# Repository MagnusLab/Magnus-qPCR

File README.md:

# 
An open, portable and low cost qPCR machine.

## WE ARE ACCEPTING [DONATIONS](https://www.vakinha.com.br/vaquinha/nos-ajude-a-desenvolver-uma-maquina-de-qpcr-a-baixo-custo)!: 

## Specifications*:
* 8 samples
* 1 to 4 channels, you can customize it!
  * FAM/Sybr Green
  * HEX
  * ROX/Cal Red 610
  * Cy5
* MicroSD card slot for data logging
* High Resolution Melting Analysis
* WiFi interface, so you can control and visualize data from a smartphone/PC
* Portable (less than 150 mm in size)
* USB powered (5V 3A power supply)
* CHEAP

**This machine is a work in progress, so the specifications may change and/or be innacurate. Also, don't try to replicate it if you don't know what you're doing, as it probably won't work until we release a stable version.*

## How will it work?
The machine can be roughly separated into 3 parts:

* The main PCB, containing the microcontroller and the heater;
* The PCB of the reading head, containing LEDs and light sensors;
* The optical reading head, which will house lenses, beam splitters, filters, prisms, etc., as well as the stepper motor responsible for positioning this optical assembly above each tube;

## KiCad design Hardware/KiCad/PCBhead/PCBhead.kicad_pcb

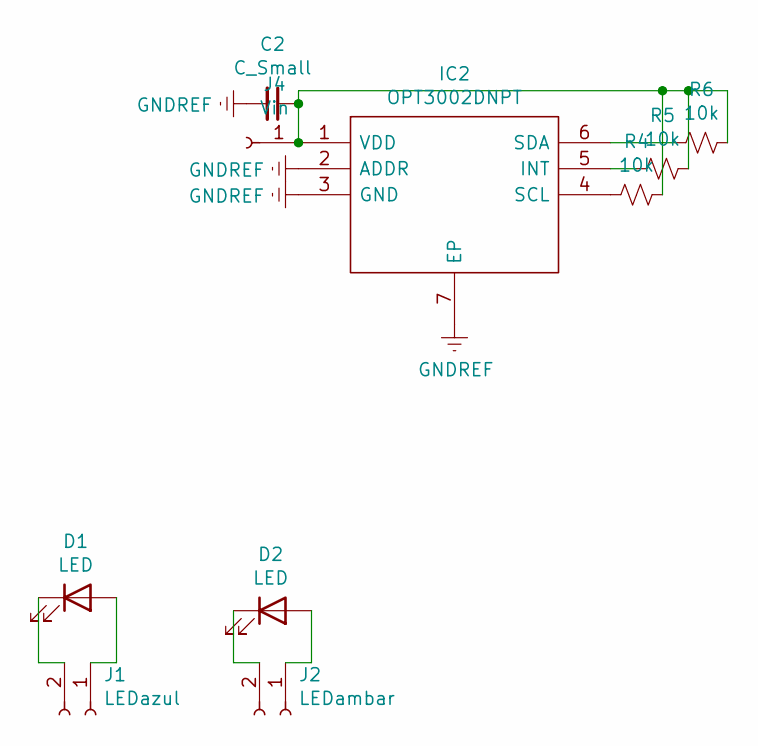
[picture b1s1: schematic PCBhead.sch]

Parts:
C2: C_Small; C_0805_2012Metric
D1, D2: LED
IC2: OPT3002DNPT; SON65P200X200X65-7N-D; Mouser Part Number 595-OPT3002DNPT
J1: LEDazul; PinSocket_1x02_P2.54mm_Horizontal
J2: LEDambar; PinSocket_1x02_P2.54mm_Horizontal
J4: Vin; PinSocket_1x01_P2.54mm_Horizontal
R4, R5, R6: 10k; R_0805_2012Metric

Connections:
GNDREF: C2.2, IC2.2 (ADDR), IC2.3 (GND), IC2.7 (EP)
unnamed: C2.1, IC2.1 (VDD), J4.1, R4.1, R5.1, R6.1
unnamed: D1.1 (K), J1.2
unnamed: D1.2 (A), J1.1
unnamed: D2.1 (K), J2.2
unnamed: D2.2 (A), J2.1
unnamed: IC2.4 (SCL), R4.2
unnamed: IC2.5 (INT), R5.2
unnamed: IC2.6 (SDA), R6.2

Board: 2 copper layers, 10 parts (7 on the bottom side), 9 nets, no tracks yet.

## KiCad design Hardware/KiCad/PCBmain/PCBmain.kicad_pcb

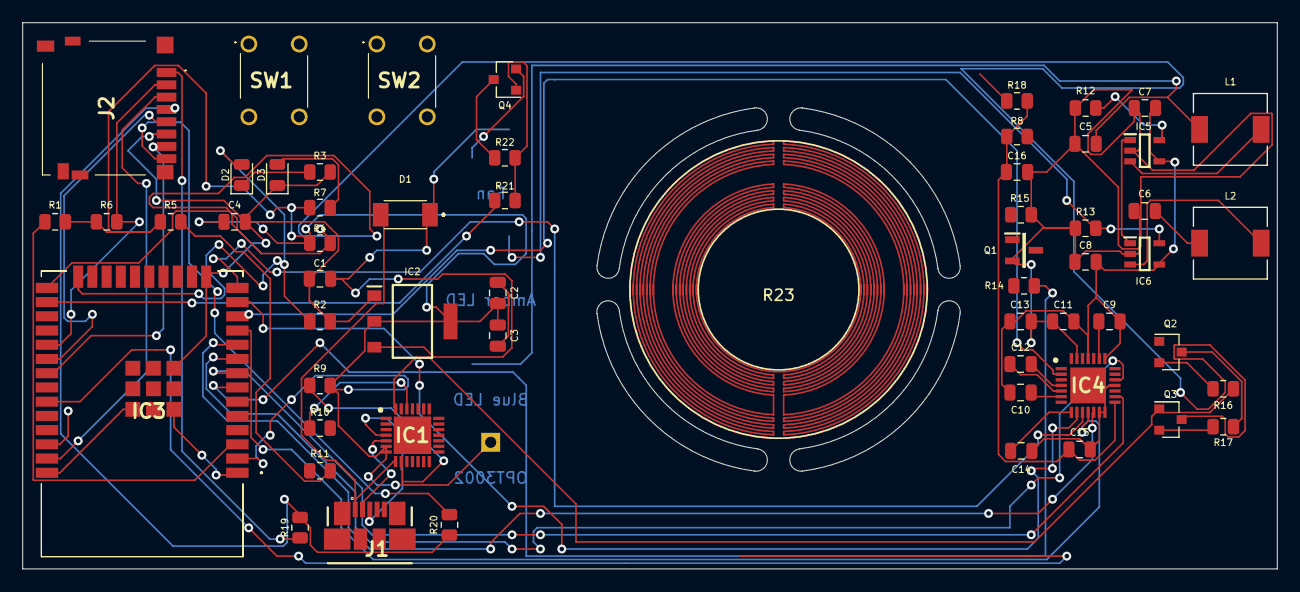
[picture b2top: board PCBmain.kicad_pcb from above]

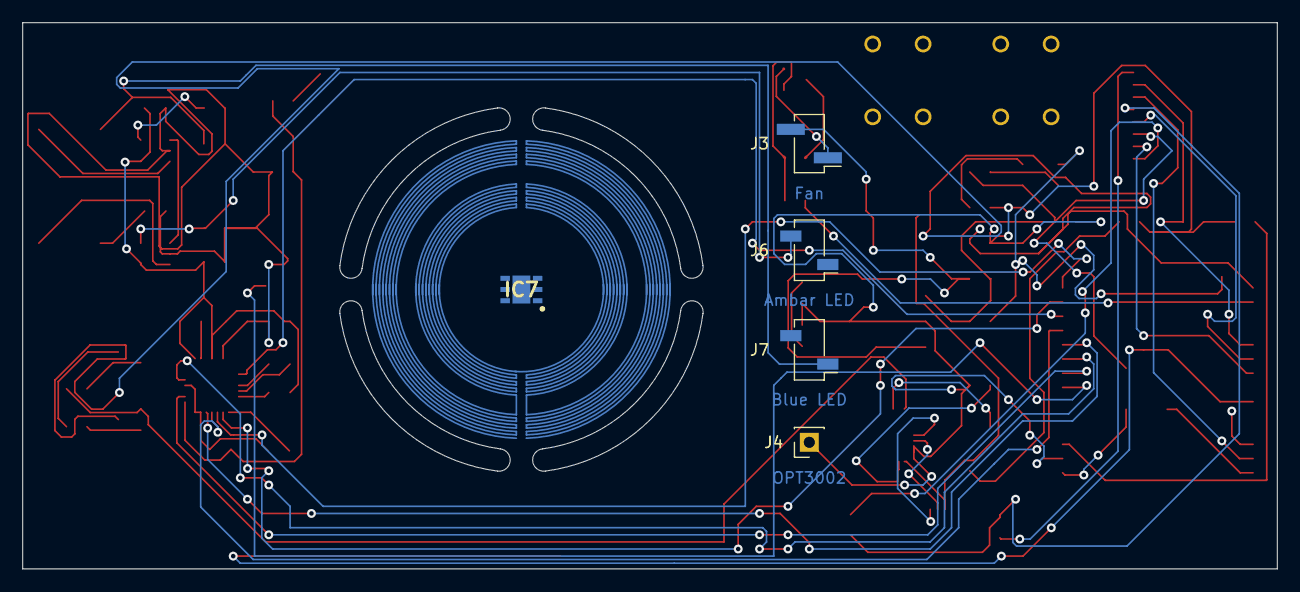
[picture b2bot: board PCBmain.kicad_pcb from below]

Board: 2 copper layers, 112.0 x 48.8 mm, 63 parts (5 on the bottom side), 53 nets.

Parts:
C1, C3, C5, C6, C7, C8: 10µF; C_0805_2012Metric
C2, C11, C13, C15: 100nF; C_0805_2012Metric
C4: 100µF 6.3V; C_0805_2012Metric
C9: 100µF; C_0805_2012Metric
C10: 22nF 50V; C_0805_2012Metric
C12: 100nF 16V; C_0805_2012Metric
C14: 2.2µF 6.3V; C_0805_2012Metric
C16: 0.1µF; C_0805_2012Metric
D1: D_Schottky_Small; PMEG3050EP115
D2, D3: LED; LED_0805_2012Metric
IC1: CP2102; QFN50P500X500X100-29N-D
IC2: NCP1117ST33T3G; SOT230P700X180-4N
IC3: ESP32-WROOM-32_M103QH3200PH3Q0_; ESP32WROOM32M103QH3200PH3Q0
IC4: TMC2208-LA-T; QFN50P500X500X90-29N-D
IC5, IC6: PAM2804AAB010; SOT95P280X100-5N
IC7: TMP117AIDRVT; SON100P300X300X80-7N-D
J1: 47346-0001
J2: DM3D-SF; DM3DSF
J3: fan; PinHeader_1x02_P2.54mm_Vertical_SMD_Pin1Left
J4: OPT3002; PinSocket_1x01_P2.54mm_Vertical
J6: LEDambar; PinSocket_1x02_P2.54mm_Vertical_SMD_Pin1Left
J7: LEDazul; PinSocket_1x02_P2.54mm_Vertical_SMD_Pin1Left
L1, L2: 4,7µH; L_6.3x6.3_H3
Q1: IRLML6244TRPBF; SOT95P237X112-3N
Q2, Q3: S8050; SOT-23
Q4: Q_NMOS_GDS; SOT-23
R1, R2, R4, R5, R6, R8, R15, R16, R17, R18, R19, R20, R22: 10k; R_0805_2012Metric
R3, R7, R10, R11: 1k; R_0805_2012Metric
R9: 4.7k; R_0805_2012Metric
R12, R13: ?; R_0805_2012Metric
R14, R21: 200; R_0805_2012Metric
R23: Heater; aquecedor
SW1, SW2: SW_Push; TS665CJ

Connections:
/3.3V: J2.4, R19.2, R20.1
/CLK: IC3.30, J2.5
/CMD: IC3.37, J2.3
/D+: IC1.4, J1.3
/D-: IC1.5, J1.2
/DAT0: IC3.31, J2.7
/DIAG: IC3.11, IC4.11
/DIR: IC3.9, IC4.19
/DTR: IC1.28, Q3.1, R16.1
/EN: IC3.3, Q2.1, R1.1
/ENN: IC3.12, IC4.2
/GPIO0: IC3.25, Q3.3, R4.2
/GPIO2: D2.2, IC3.24, R2.1
/GPIO5: IC3.29, J2.2, R6.2
/INDEX: IC3.10, IC4.12
/LEDamar+: C6.2, L2.1
/LEDambar-: IC6.5, J6.2, R13.2
/LEDazul+: C5.2, J7.1, L1.1
/LEDazul-: IC5.5, J7.2, R12.2
/MS1: IC3.13, IC4.9
/MS2: IC3.14, IC4.10
/Mosfet: Q1.3, R23.2
/PWMaquecedor: IC3.7, R14.2
/PWMled: IC3.6, IC5.1, IC6.1
/RTS: IC1.24, Q2.3, R17.1
/SCL: IC3.36, IC7.1, R8.2
/SDA: IC3.33, IC7.6, R18.2
/STEP: IC3.8, IC4.16
/TX0: R5.2, R11.2
/VCC_USB: D1.2, IC1.8, J1.1
/VDD_3.3V: C2.2, C3.1, C4.1, C15.1, C16.1, IC1.6, IC1.7, IC2.2, IC2.4, IC3.2, IC4.15, IC7.5, J4.1, R1.2, R4.1, R5.1, R6.1, R7.1, R8.1, R9.2, R18.1
/Vin: C1.1, C7.2, C8.2, C9.1, C10.2, C11.2, C13.2, D1.1, IC2.3, IC4.22, IC4.25, IC5.4, IC6.4, J3.2, R23.1
/fan: IC3.26, R21.1
/stepperMotor: IC4.1, IC4.21, IC4.24, IC4.26
GNDREF: C1.2, C2.1, C3.2, C4.2, C5.1, C6.1, C7.1, C8.1, C9.2, C11.1, C13.1, C14.1, C15.2, C16.2, D3.1, IC2.1, IC3.1, IC3.15, IC3.38, IC3.39, IC3.40, IC3.41, IC3.42, IC3.43, IC3.44, IC3.45, IC3.46, IC3.47, IC4.3, IC4.13, IC4.14, IC4.18, IC4.23, IC4.27, IC4.29, IC5.2, IC6.2, IC7.2, J1.5, J2.6, Q1.2, Q4.3, R2.2, R3.2, R12.1, R13.1, R15.1, R22.1
unnamed: C10.1, IC4.6
unnamed: C12.1, IC4.5
unnamed: C12.2, IC4.4
unnamed: C14.2, IC4.8
unnamed: D2.1, R3.1
unnamed: D3.2, R7.2
unnamed: IC1.9, R9.1
unnamed: IC1.25, R11.1
unnamed: IC1.26, R10.1
unnamed: IC5.3, L1.2
unnamed: IC6.3, L2.2
unnamed: J2.1, R19.1
unnamed: J2.8, R20.2
unnamed: J3.1, Q4.2
unnamed: Q1.1, R14.1, R15.2
unnamed: Q2.2, R16.2
unnamed: Q3.2, R17.2
unnamed: Q4.1, R21.2, R22.2

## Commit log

2021-03-04 opticalBench pic and mechanical parts
2021-03-04 media
2021-03-04 MainPCB_Schematics
2021-03-04 Adicionando projeto do KiCad
2021-03-05 english descriptions on the images
2021-03-06 logo
2021-03-08 footprintsHeatersTests
2021-03-08 head update
2021-03-09 heatersTest
